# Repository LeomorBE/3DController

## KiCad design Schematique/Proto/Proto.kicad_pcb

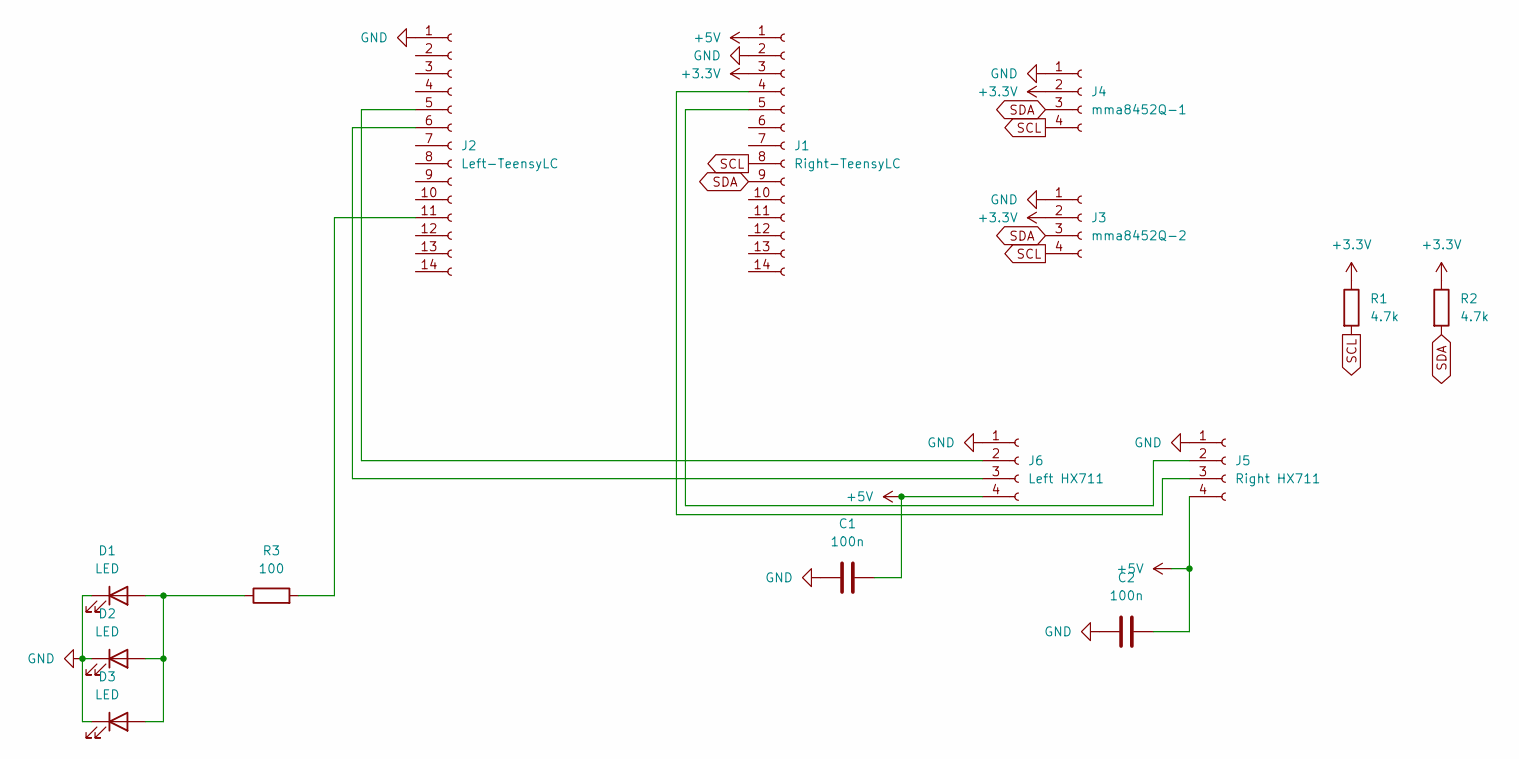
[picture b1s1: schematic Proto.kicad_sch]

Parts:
C1, C2: 100n; C_0805_2012Metric_Pad1.18x1.45mm_HandSolder
D1, D2, D3: LED; LED_D5.0mm
J1: Right-TeensyLC; PinHeader_1x14_P2.54mm_Vertical
J2: Left-TeensyLC; PinHeader_1x14_P2.54mm_Vertical
J3: mma8452Q-2; PinHeader_1x04_P2.54mm_Vertical
J4: mma8452Q-1; PinHeader_1x04_P2.54mm_Vertical
J5: Right HX711; PinHeader_1x04_P2.54mm_Vertical
J6: Left HX711; PinHeader_1x04_P2.54mm_Vertical
R1, R2: 4.7k; R_Axial_DIN0309_L9.0mm_D3.2mm_P15.24mm_Horizontal
R3: 100; R_Axial_DIN0309_L9.0mm_D3.2mm_P15.24mm_Horizontal

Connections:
+3.3V: J1.3, J3.2, J4.2, R1.1, R2.1
+5V: C1.2, C2.2, J1.1, J5.4, J6.4
GND: C1.1, C2.1, D1.1 (K), D2.1 (K), D3.1 (K), J1.2, J2.1, J3.1, J4.1, J5.1, J6.1
unnamed: D1.2 (A), D2.2 (A), D3.2 (A), R3.1
unnamed: J1.4, J5.3
unnamed: J1.5, J5.2
unnamed: J2.5, J6.2
unnamed: J2.6, J6.3
unnamed: J2.11, R3.2
SCL: J1.8, J3.4, J4.4, R1.2
SDA: J1.9, J3.3, J4.3, R2.2

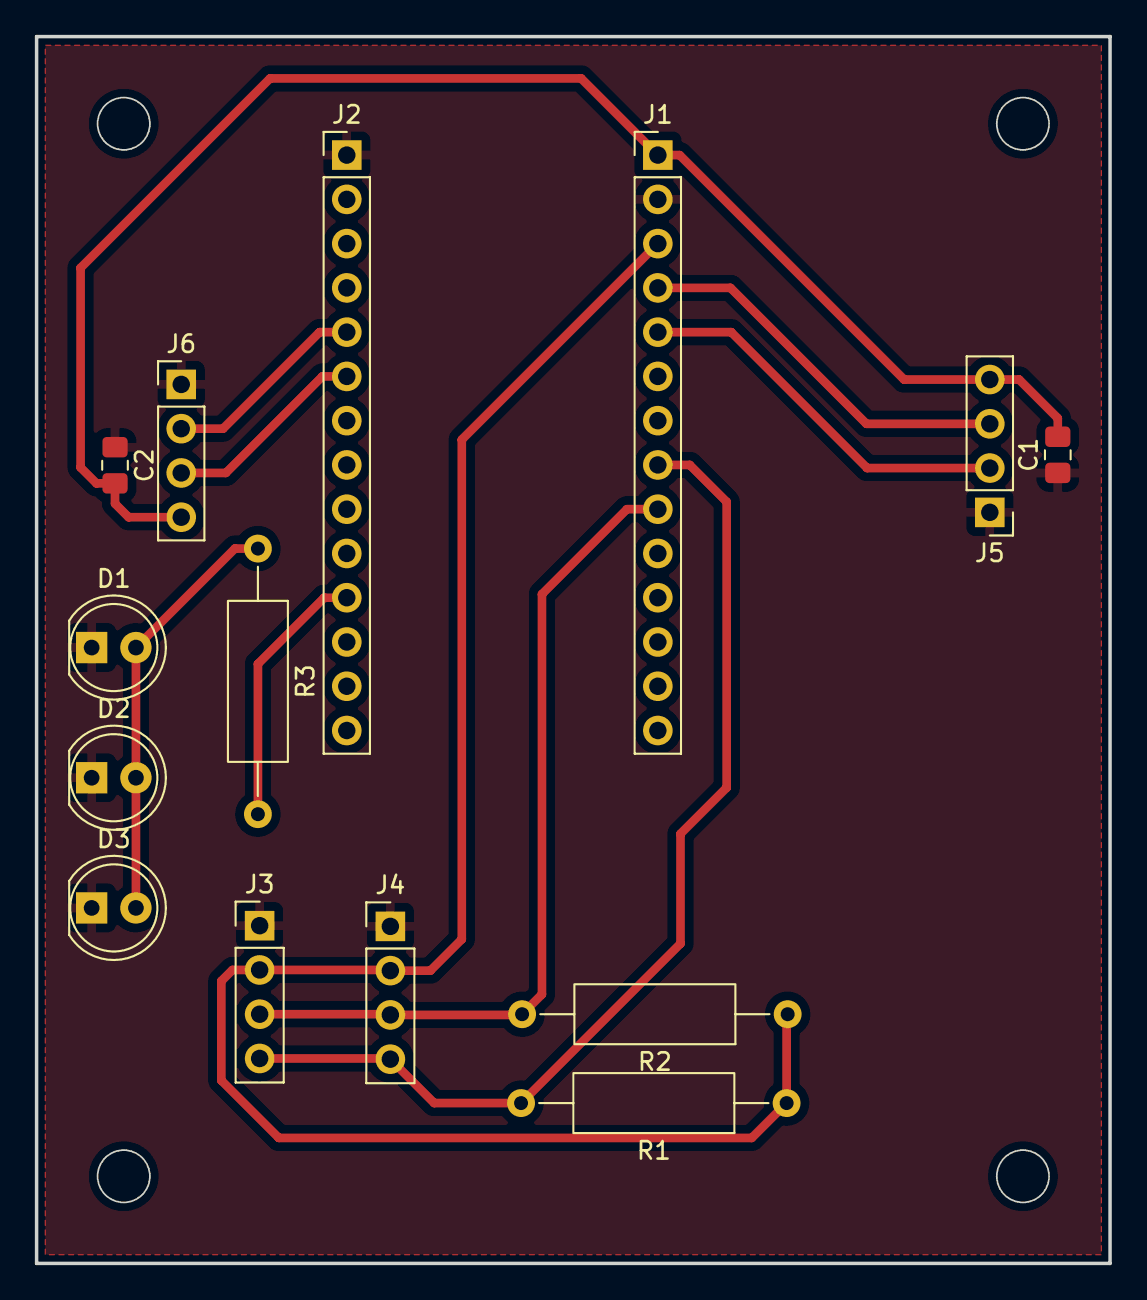
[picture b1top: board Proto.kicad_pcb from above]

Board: 2 copper layers, 61.6 x 70.4 mm, 14 parts (0 on the bottom side), 11 nets.
